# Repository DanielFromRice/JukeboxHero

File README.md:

# JukeboxHero
ELEC327 Final Project

Team CLARG:
Mac Carr
Kevin Lata
Michael Angino
Daniel Rothfusz
Elise Gibney

In this project, we are using MSP430G2553 microcontrollers to play a 
version of Guitar Hero.

There are 3 distinct PCBs:
	1. Controller Board
	2. Speaker Boards
	3. Break Beam Boards

1. Controller Board:
This board functions as a central controller module. It facilitates song 
selection, loading data from the SD card, managing a timing module, and 
commmunicating data to the other modules. The SD card uses SPI communication
implementing the PetitFs library (http://elm-chan.org/fsw/ff/00index_p.html)
Song selection is done using 3 buttons, implementing up, down, and select.
Support for a display module is intended for future development.

2. Speaker Boards:
These boards basically consist of a speaker and an MSP430. They wait to 
receive a signal from the controller over I2C, and when they do, they 
change their frequency with the new data they have received.

3. Break Beam Boards: 
This board facilitates communication to the DotStar LED strips and 
to the breakbeam sensors. This board is preloaded with break beam song data
once a song has been selected, and then proceeds to advance the lights and 
track a user's score as it receives notice from the central controller.

Overall, the game should function similarly to Guitar Hero. Lights descend 
along the DotStar strips, signaling which beam break sensor the player should
trip. The order of these loosely correspond to a song that is playing, which
produces multiple tones over a collection of piezzo buzzers. 

To run:
Once boards are wired up with the appropriate hardware, open 3 projects in 
Code Composer Studio. Load all the code from ControllerBoardCode to the 
Controller board, load code from the Break_Beam folder to the Break Beam 
Board, and load the code from SpeakerBoardCode to each speaker board, 
ensuring that each one gets a different I2C address.

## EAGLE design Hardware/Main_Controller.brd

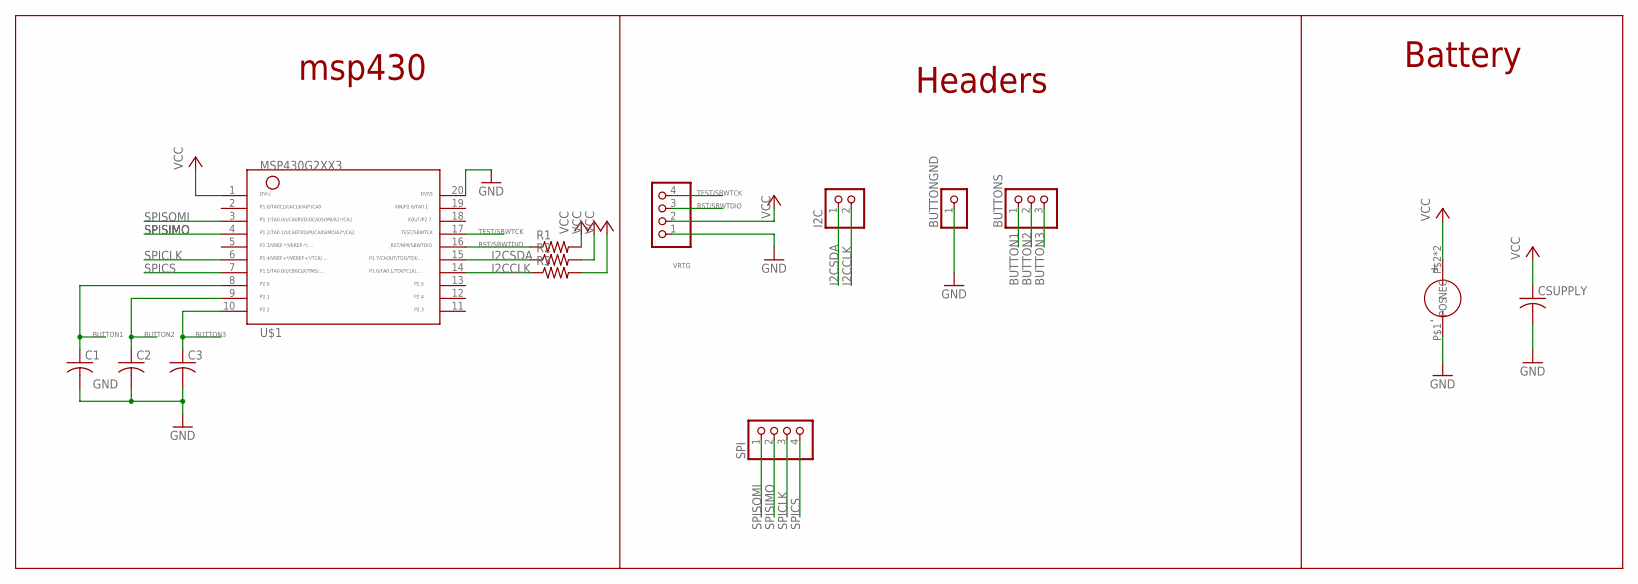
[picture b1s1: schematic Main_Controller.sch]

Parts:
BUTTONGND: PINHD-1X1; 1X01
BUTTONS: PINHD-1X3; 1X03
C1, C2, C3: C-USC1206; C1206
CSUPPLY: C-USC1206; C1206
I2C: PINHD-1X2; 1X02
R1, R2, R3: R-US_R1206; R1206
SPI: PINHD-1X4; 1X04
U$1: MSP430G2XX3TSSOP; PW20
U$2: 3002BATTERY
VRTG: PINHD-1X4; 1X04

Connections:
BUTTON1: BUTTONS.1, C1.1, U$1.8
BUTTON2: BUTTONS.2, C2.1, U$1.9
BUTTON3: BUTTONS.3, C3.1, U$1.10
GND: BUTTONGND.1, C1.2, C2.2, C3.2, CSUPPLY.2, U$1.20, U$2.P$1 (NEG), VRTG.1
I2CCLK: I2C.2, R3.1, U$1.14
I2CSDA: I2C.1, R2.1, U$1.15
RST/SBWTDIO: R1.1, U$1.16, VRTG.3
SPICLK: SPI.3, U$1.6
SPICS: SPI.4, U$1.7
SPISIMO: SPI.2, U$1.4
SPISOMI: SPI.1, U$1.3
TEST/SBWTCK: U$1.17, VRTG.4
VCC: CSUPPLY.1, R1.2, R2.2, R3.2, U$1.1, U$2.P$2 (POS), U$2.P$3 (POS), VRTG.2

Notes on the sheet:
msp430
Headers
Battery

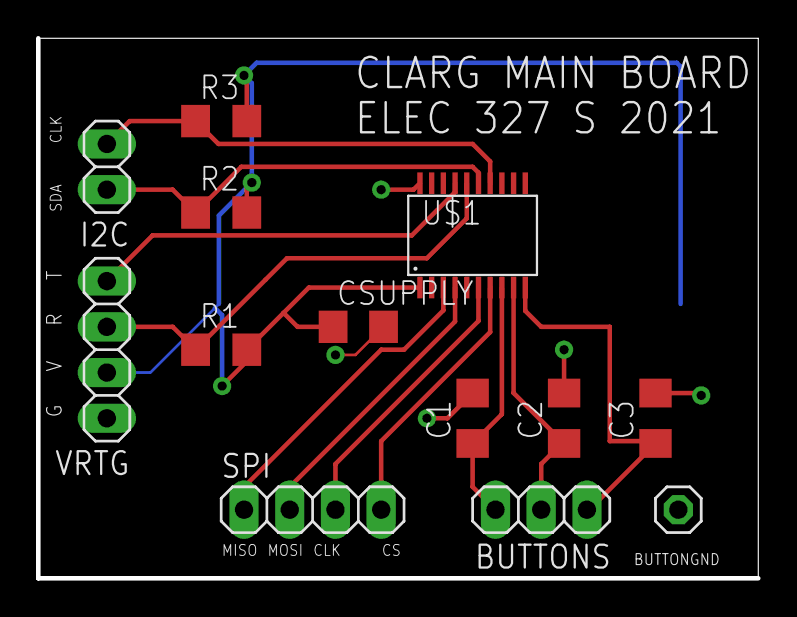
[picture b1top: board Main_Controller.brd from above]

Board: 2 copper layers, 40.0 x 30.0 mm, 14 parts (1 on the bottom side), 13 nets.

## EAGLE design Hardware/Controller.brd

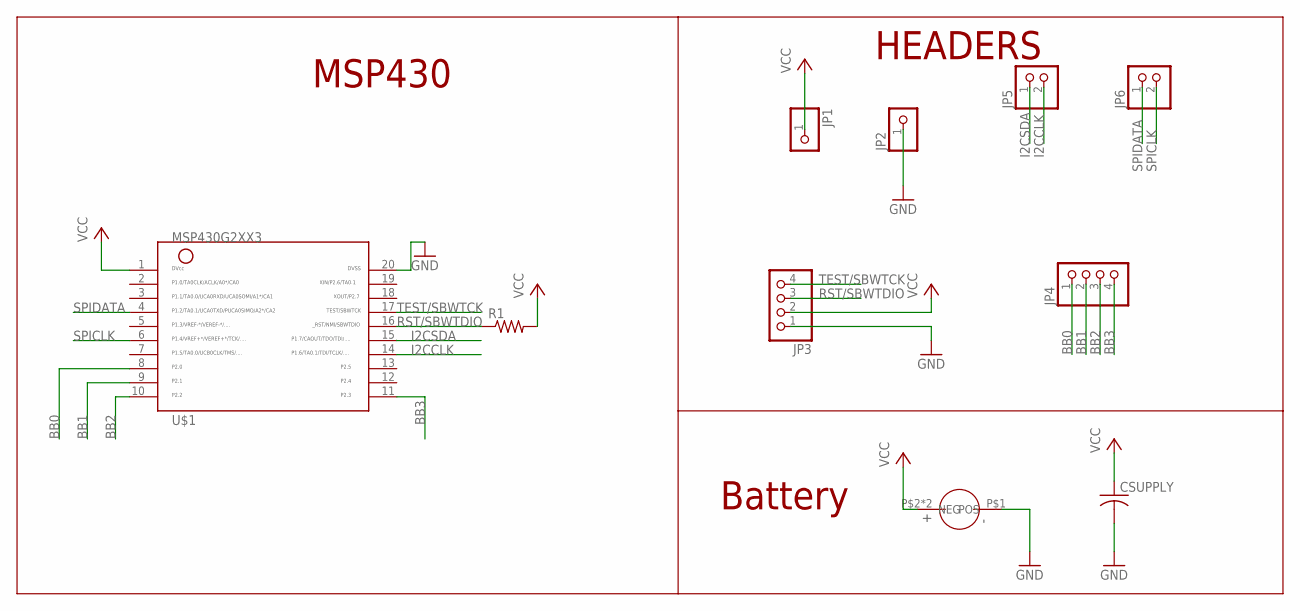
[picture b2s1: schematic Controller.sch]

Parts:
CSUPPLY: C-USC1206; C1206
JP1, JP2: PINHD-1X1; 1X01
JP3, JP4: PINHD-1X4; 1X04
JP5, JP6: PINHD-1X2; 1X02
R1: R-US_R1206; R1206
U$1: MSP430G2XX3TSSOP; PW20
U$2: 3002BATTERY

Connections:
BB0: JP4.1, U$1.8
BB1: JP4.2, U$1.9
BB2: JP4.3, U$1.10
BB3: JP4.4, U$1.11
GND: CSUPPLY.2, JP2.1, JP3.1, U$1.20, U$2.P$1 (NEG)
I2CCLK: JP5.2, U$1.14
I2CSDA: JP5.1, U$1.15
RST/SBWTDIO: JP3.3, R1.1, U$1.16
SPICLK: JP6.2, U$1.6
SPIDATA: JP6.1, U$1.4
TEST/SBWTCK: JP3.4, U$1.17
VCC: CSUPPLY.1, JP1.1, JP3.2, R1.2, U$1.1, U$2.P$2 (POS), U$2.P$3 (POS)

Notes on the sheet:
MSP430
HEADERS
Battery

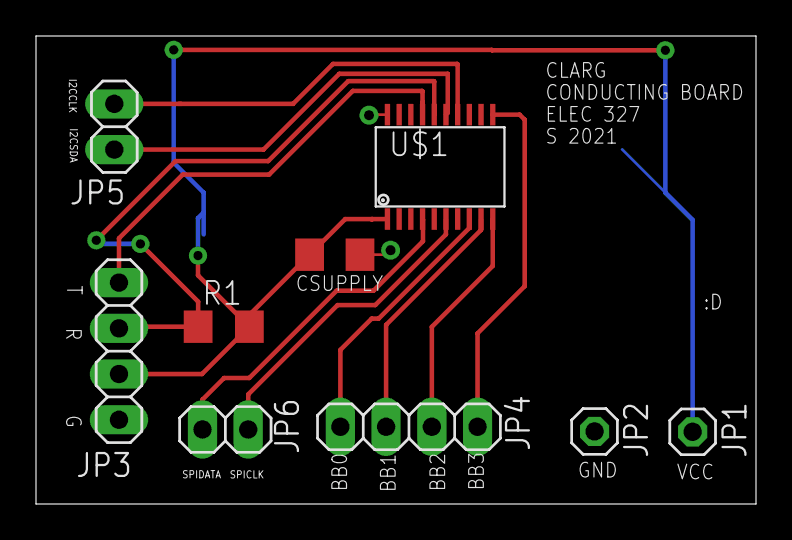
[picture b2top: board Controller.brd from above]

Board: 2 copper layers, 40.0 x 26.0 mm, 10 parts (1 on the bottom side), 12 nets.

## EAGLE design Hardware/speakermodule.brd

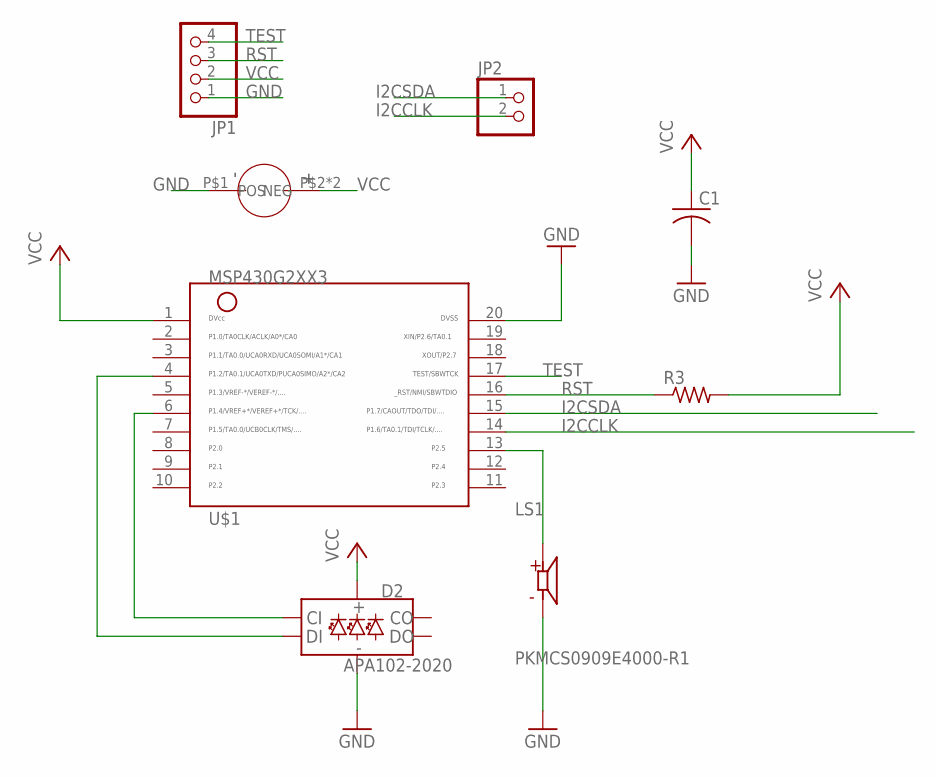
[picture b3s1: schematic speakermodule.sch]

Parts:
C1: C-USC1206; C1206
D2: APA102-2020
JP1: PINHD-1X4; 1X04
JP2: PINHD-1X2; 1X02
LS1: PKMCS0909E4000-R1; SPKR_PKMCS0909E4000-R1
R3: R-US_R1206; R1206
U$1: MSP430G2XX3TSSOP; PW20
U$3: 3002BATTERY

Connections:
GND: C1.2, D2.GND, JP1.1, LS1.2 (N), U$1.20, U$3.P$1 (NEG)
I2CCLK: JP2.2, U$1.14
I2CSDA: JP2.1, U$1.15
unnamed: LS1.1, U$1.13
unnamed: D2.CKI (CI), U$1.6
unnamed: D2.SDI (DI), U$1.4
RST: JP1.3, R3.1, U$1.16
TEST: JP1.4, U$1.17
VCC: C1.1, D2.VDD (VCC), JP1.2, R3.2, U$1.1, U$3.P$2 (POS), U$3.P$3 (POS)

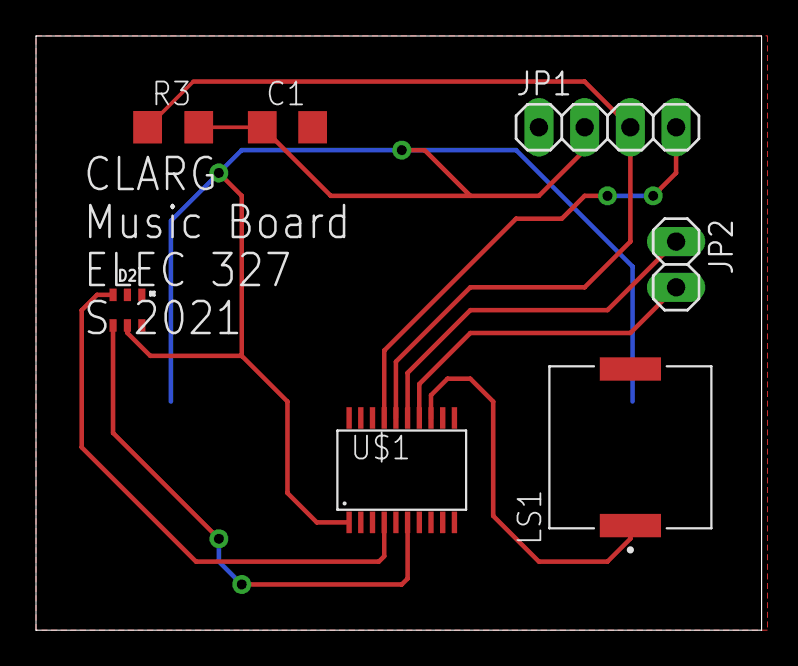
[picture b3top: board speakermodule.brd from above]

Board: 2 copper layers, 40.3 x 33.0 mm, 8 parts (1 on the bottom side), 9 nets.

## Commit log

2021-04-19 Added initial files and controller board scematics
2021-04-19 Create gitignore
2021-04-19 remove extra gitignore
2021-04-19 Added Speaker Eagle Files
2021-04-21 Main Board rough draft finished
2021-04-21 main board draft 2
2021-04-21 added git ignore file
2021-04-21 removed backup files
2021-04-21 controller board draft 1
2021-04-21 added capacitor to main board
2021-04-21 Added libraries
2021-04-21 Renamed Battery Library
2021-04-21 Resized Main Board Name
2021-04-21 resized controller board name
2021-04-21 removed extra i2c resistors
2021-04-22 Speaker Module
2021-04-22 cam jobs and battery updates for controller and speaker boards
2021-04-22 main board battery issue changes and cam job
2021-05-06 Preliminary SD card code, not yet shifted to USCIA
2021-05-06 Changed ports to USCI USA0
2021-05-10 added control send and follower recieve code
2021-05-10 First draft of pseudocode from Daniel
2021-05-10 Updated SD code to be modular
2021-05-10 Added speaker board code, need to update addresses
2021-05-10 Controller Board Code v1
2021-05-10 Fixed build on Controller Code
2021-05-11 Fixed ports for speakerboard
2021-05-11 Updated Controller board to use buttons
2021-05-11 Binary conversion from csv files
2021-05-11 updated speaker code so it works
2021-05-11 added inital beam board code
2021-05-11 Formatted csv parser working
2021-05-11 Lida Rose Ready
2021-05-11 All Star binary file created
2021-05-11 SD test code
2021-05-11 Fixed Packet size, Lida Rose Code
2021-05-11 All Star binary updated to new format
2021-05-11 updated beam board code
2021-05-12 Long night's work code
2021-05-12 Debug and testing in lab
2021-05-12 Reorganization and README
2021-05-13 Added comments
2021-05-13 Display Change comments
2021-05-13 Controller board comments

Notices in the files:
parts and their libraries:
SparkFun-LED: Licensing: Creative Commons ShareAlike 4.0 International - https://creativecommons.org/licenses/by-sa/4.0
